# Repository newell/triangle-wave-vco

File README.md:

# Triangle Wave Voltage-Controlled Oscillator (VCO)

A Triangle Wave Voltage-Controlled Oscillator (VCO) is an electronic oscillator that generates a triangle waveform as its output. It is a type of voltage-controlled oscillator where the frequency of oscillation is controlled by an input voltage.

The basic configuration of a Triangle Wave VCO consists of an integrator circuit and a comparator. The integrator circuit integrates the output of the comparator, producing a ramp or linearly increasing voltage waveform. The comparator compares this ramp waveform with a reference voltage or a control voltage. Whenever the ramp waveform reaches the reference voltage, the comparator flips its output state, causing the integrator to change direction and generate a ramp in the opposite direction. This process repeats, resulting in a triangle waveform at the output.

By varying the control voltage applied to the VCO, the slope or rate at which the ramp waveform increases or decreases can be adjusted, thereby controlling the frequency of the triangle wave output. Higher control voltages result in a steeper slope and higher frequency, while lower control voltages result in a shallower slope and lower frequency.

Triangle wave VCOs are commonly used in various applications, including audio synthesis, modulation techniques, and frequency modulation (FM) systems. They provide a means of generating a continuous, linearly increasing and decreasing waveform with controllable frequency.

<!--  -->

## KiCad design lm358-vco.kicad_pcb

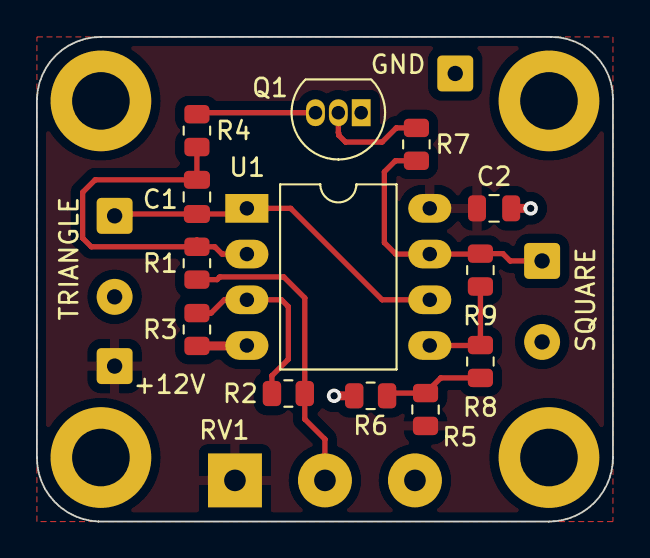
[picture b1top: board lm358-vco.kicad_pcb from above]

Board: 2 copper layers, 32.0 x 26.9 mm, 18 parts (0 on the bottom side), 11 nets.

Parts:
+12V: Conn_01x01; SolderWire-0.25sqmm_1x01_D0.65mm_OD2mm
C1: 47nF; C_0805_2012Metric
C2: 0.1uF; C_0805_2012Metric
GND: Conn_01x01; SolderWire-0.25sqmm_1x01_D0.65mm_OD2mm
Q1: 2N3904; TO-92_Inline
R1, R5, R6, R9: 100k; R_0805_2012Metric
R2, R3, R8: 51k; R_0805_2012Metric
R4: 49.9k; R_0805_2012Metric
R7: 10k; R_0805_2012Metric
RV1: 20k; Potentiometer_Alps_RK163_Single_Horizontal
SQUARE: Conn_Coaxial; SolderWire-0.25sqmm_1x02_P4.5mm_D0.65mm_OD2mm
TRIANGLE: Conn_Coaxial; SolderWire-0.25sqmm_1x02_P4.5mm_D0.65mm_OD2mm
U1: LM358; DIP-8_W10.16mm_LongPads

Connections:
+12V: +12V.1, C2.1, R5.2, RV1.1, U1.8 (V+)
GNDREF: C2.2, GND.1, Q1.1 (E), R3.1, R6.1, RV1.3, SQUARE.2 (Ext), TRIANGLE.2 (Ext), U1.4 (V-)
unnamed: C1.1, R1.2, R4.1, U1.2 (-)
unnamed: C1.2, TRIANGLE.1 (In), U1.1, U1.6 (-)
unnamed: R7.2, R9.2, SQUARE.1 (In), U1.7
unnamed: Q1.2 (B), R7.1
unnamed: Q1.3 (C), R4.2
unnamed: R1.1, R2.1, RV1.2
unnamed: R2.2, R3.2, U1.3 (+)
unnamed: R5.1, R6.2, R8.2
unnamed: R8.1, R9.1, U1.5 (+)

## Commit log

2023-06-27 Add .gitignore
2023-06-27 Add datasheet for lm358
2023-06-27 Add schematic
2023-06-27 Add pcb
2023-06-27 Update changes
2023-07-14 Add directory for datasheets
2023-07-14 Update schematic and change file names to match new repository name.
